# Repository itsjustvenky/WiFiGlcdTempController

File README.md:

#WiFiGlcdTempController
An ESP8266-based WiFi Temperature Controller that uses Avahi for network discovery, 1-Wire DS18B20 Digital Thermometers, DS2406+ Digital Switches, and a Color 320x240 TFT Display, using the ILI9341 Controller Chip.

##Programming Environment
All of my coding was done using an ESP-12 board and the ESP8266 Arduino IDE described at <a href="https://github.com/esp8266/Arduino" target="_blank">https://github.com/esp8266/Arduino</a> and using a simple <a href="http://smile.amazon.com/gp/product/B00F2F5HVK?psc=1&redirect=true&ref_=oh_aui_detailpage_o02_s00" target ="_blank">Black PL2303HX USB To TTL To UART RS232 COM Cable Module Converter</a> to upload the program.

##Setup
Before using the code for the first time, I recommend clearing the EEPROM on the ESP8266 to insure that it can be set up properly. I've included 'eeprom_clear.ino' in the utilities folder for that reason.

Attach your DS18B20 Digital Thermometer and DS2406+ switches, and I2C 20x4 LCD.
 
Once the EEPROM has been cleared, compile and upload the 'WiFiGlcdTempController.ino' files. Once uploaded, make sure that the Serial monitor is open and set to '112500 baud', and 'Newline' for any text sent.

The Serial Monitor will ask for an SSID, PASSWD. Set these values to match your WiFi Network.

The Serial Monitor will then ask is you want to use DHCP to get an IP address. If you answer "Y", the ESP8266 will attempt to negotiate an IP address via DHCP. A "N" answer will result in a request for an IP address, Gateway address and Subnet Mask.

The Serial Monitor will then ask for a udpPort value. This is the port address that the board will use when communicating with the network.

If all goes well, the Serial Monitor should show the results of the attempt to access your WiFi Network.

##Using the UDPTempController

I've also included a short PHP utility that will communicate with the UdpTempController and allow the state of the chips to be monitored and set.

To use it, you'll need PHP5 and avahi-resolve installed.

On the command line enter:
`php TestUdpTempController.php esp8266.local`

The program will attempt to locate the UdpTempController, and if successful, will display the IP address of the UdpTempController, and prompt for input.

##Commands
In general, commands take the form of a single Uppercase Letter command, followed by a numeric or alpha value. single character values immediately proceed the command with no intervening spaces.
As an example, to turn on the first switch in maual mode (more about modes in a moment), the command would be `AN`.

Commands that include a numeric value have no intervening spaces. An example would be setting the Upper Temperature Value in Automatic mode: `UF80`, which sets the Upper Temperature Value to 80&deg;F

Commands that require a multi-character alpha-numeric string have an intervening space.
As an example, to re-name the local url of the WiFiGlcdTempController, the command would be `N "DomainName"`.

##Web Page and MySql
Included are web pages and a MySql file which can be used to create a web page that can monitor multiple ESP boards, display the results on a web page, save the results into a set of MySQL tables, and display a graph of the results. The updates to the page occur every two seconds, and updated data is inserted into the database every minute.

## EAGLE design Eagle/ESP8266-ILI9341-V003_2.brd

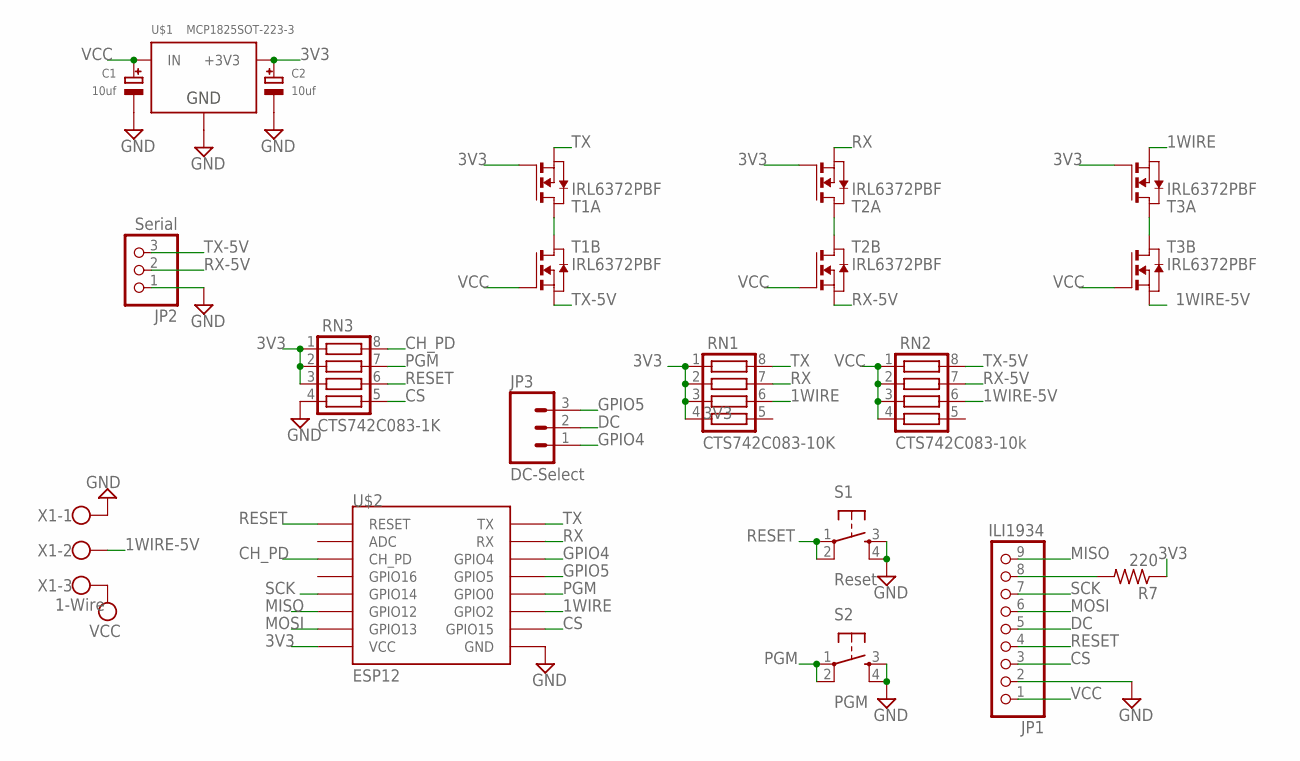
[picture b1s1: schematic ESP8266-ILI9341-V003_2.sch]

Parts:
C1, C2: 10uf; EIA3216-18/A-R
JP1: ILI1934; 1X09-BIG
JP2: Serial; 1X03
JP3: DC-Select; 1X03
R7: 220; M1206
RN1: CTS742C083-10K; CTS742C083
RN2: CTS742C083-10k; CTS742C083
RN3: CTS742C083-1K; CTS742C083
S1: Reset; TACTILE-PTH
S2: PGM; TACTILE-PTH
T1, T2, T3: IRL6372PBF; SO-8-DUAL
U$1: MCP1825SOT-223-3; SOT-223
U$2: ESP12
X1: 1-Wire; W237-103

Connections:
1WIRE: RN1.6, T3.1 (S), U$2.GPIO2
1WIRE-5V: RN2.6, T3.3 (S), X1.2
3V3: C2.+, R7.1, RN1.1, RN1.2, RN1.3, RN1.4, RN3.1, RN3.2, RN3.3, T1.2 (G), T2.2 (G), T3.2 (G), U$1.3 (+3V3), U$2.VCC
CH_PD: RN3.8, U$2.CH_PD
CS: JP1.3, RN3.5, U$2.GPIO15
DC: JP1.5, JP3.2
GND: C1.-, C2.-, JP1.2, JP2.1, RN3.4, S1.3, S1.4, S2.3, S2.4, U$1.2 (GND), U$2.GND, X1.1
GPIO4: JP3.1, U$2.GPIO4
GPIO5: JP3.3, U$2.GPIO5
MISO: JP1.9, U$2.GPIO12
MOSI: JP1.6, U$2.GPIO13
unnamed: T2.5_6 (D), T2.7_8 (D)
unnamed: T3.5_6 (D), T3.7_8 (D)
unnamed: T1.5_6 (D), T1.7_8 (D)
unnamed: JP1.8, R7.2
PGM: RN3.7, S2.1, S2.2, U$2.GPIO0
RESET: JP1.4, RN3.6, S1.1, S1.2, U$2.RESET
RX: RN1.7, T2.1 (S), U$2.RX
RX-5V: JP2.2, RN2.7, T2.3 (S)
SCK: JP1.7, U$2.GPIO14
TX: RN1.8, T1.1 (S), U$2.TX
TX-5V: JP2.3, RN2.8, T1.3 (S)
VCC: C1.+, JP1.1, RN2.1, RN2.2, RN2.3, RN2.4, T1.4 (G), T2.4 (G), T3.4 (G), U$1.1 (IN), X1.3

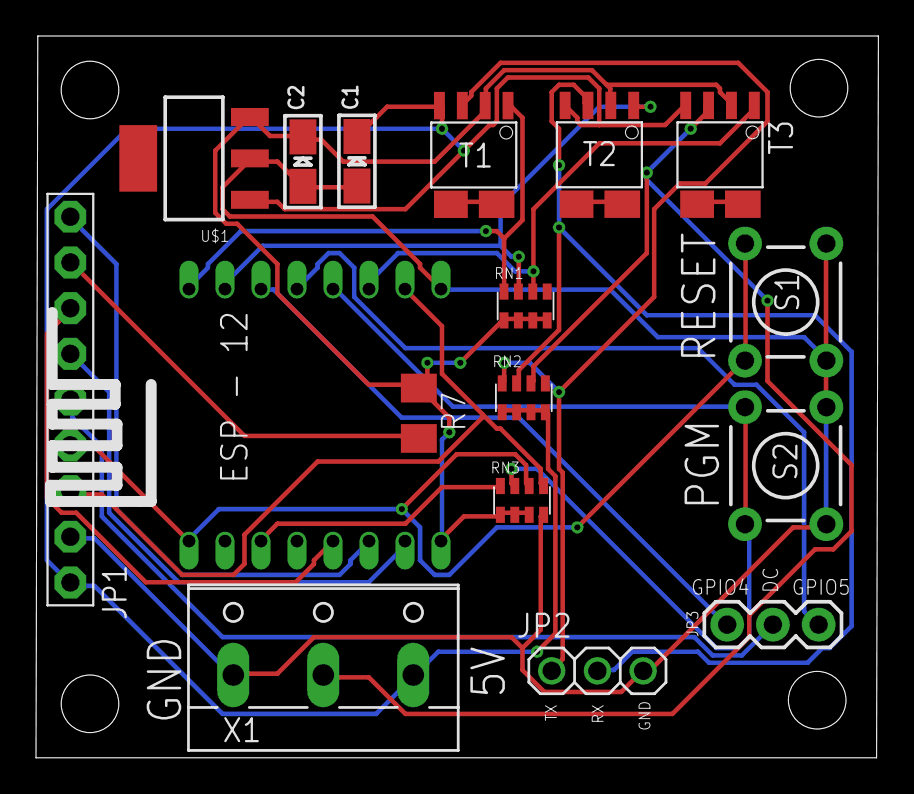
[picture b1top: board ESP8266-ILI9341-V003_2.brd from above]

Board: 2 copper layers, 46.8 x 40.1 mm, 17 parts (0 on the bottom side), 23 nets.

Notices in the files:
parts and their libraries:
microbuilder: This work is placed in the public domain, and may be freely used for commercial and non-commercial work with the following conditions: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
SparkFun-Electromechanical: Licensing: CC v3.0 Share-Alike You are welcome to use this library for commercial purposes.
